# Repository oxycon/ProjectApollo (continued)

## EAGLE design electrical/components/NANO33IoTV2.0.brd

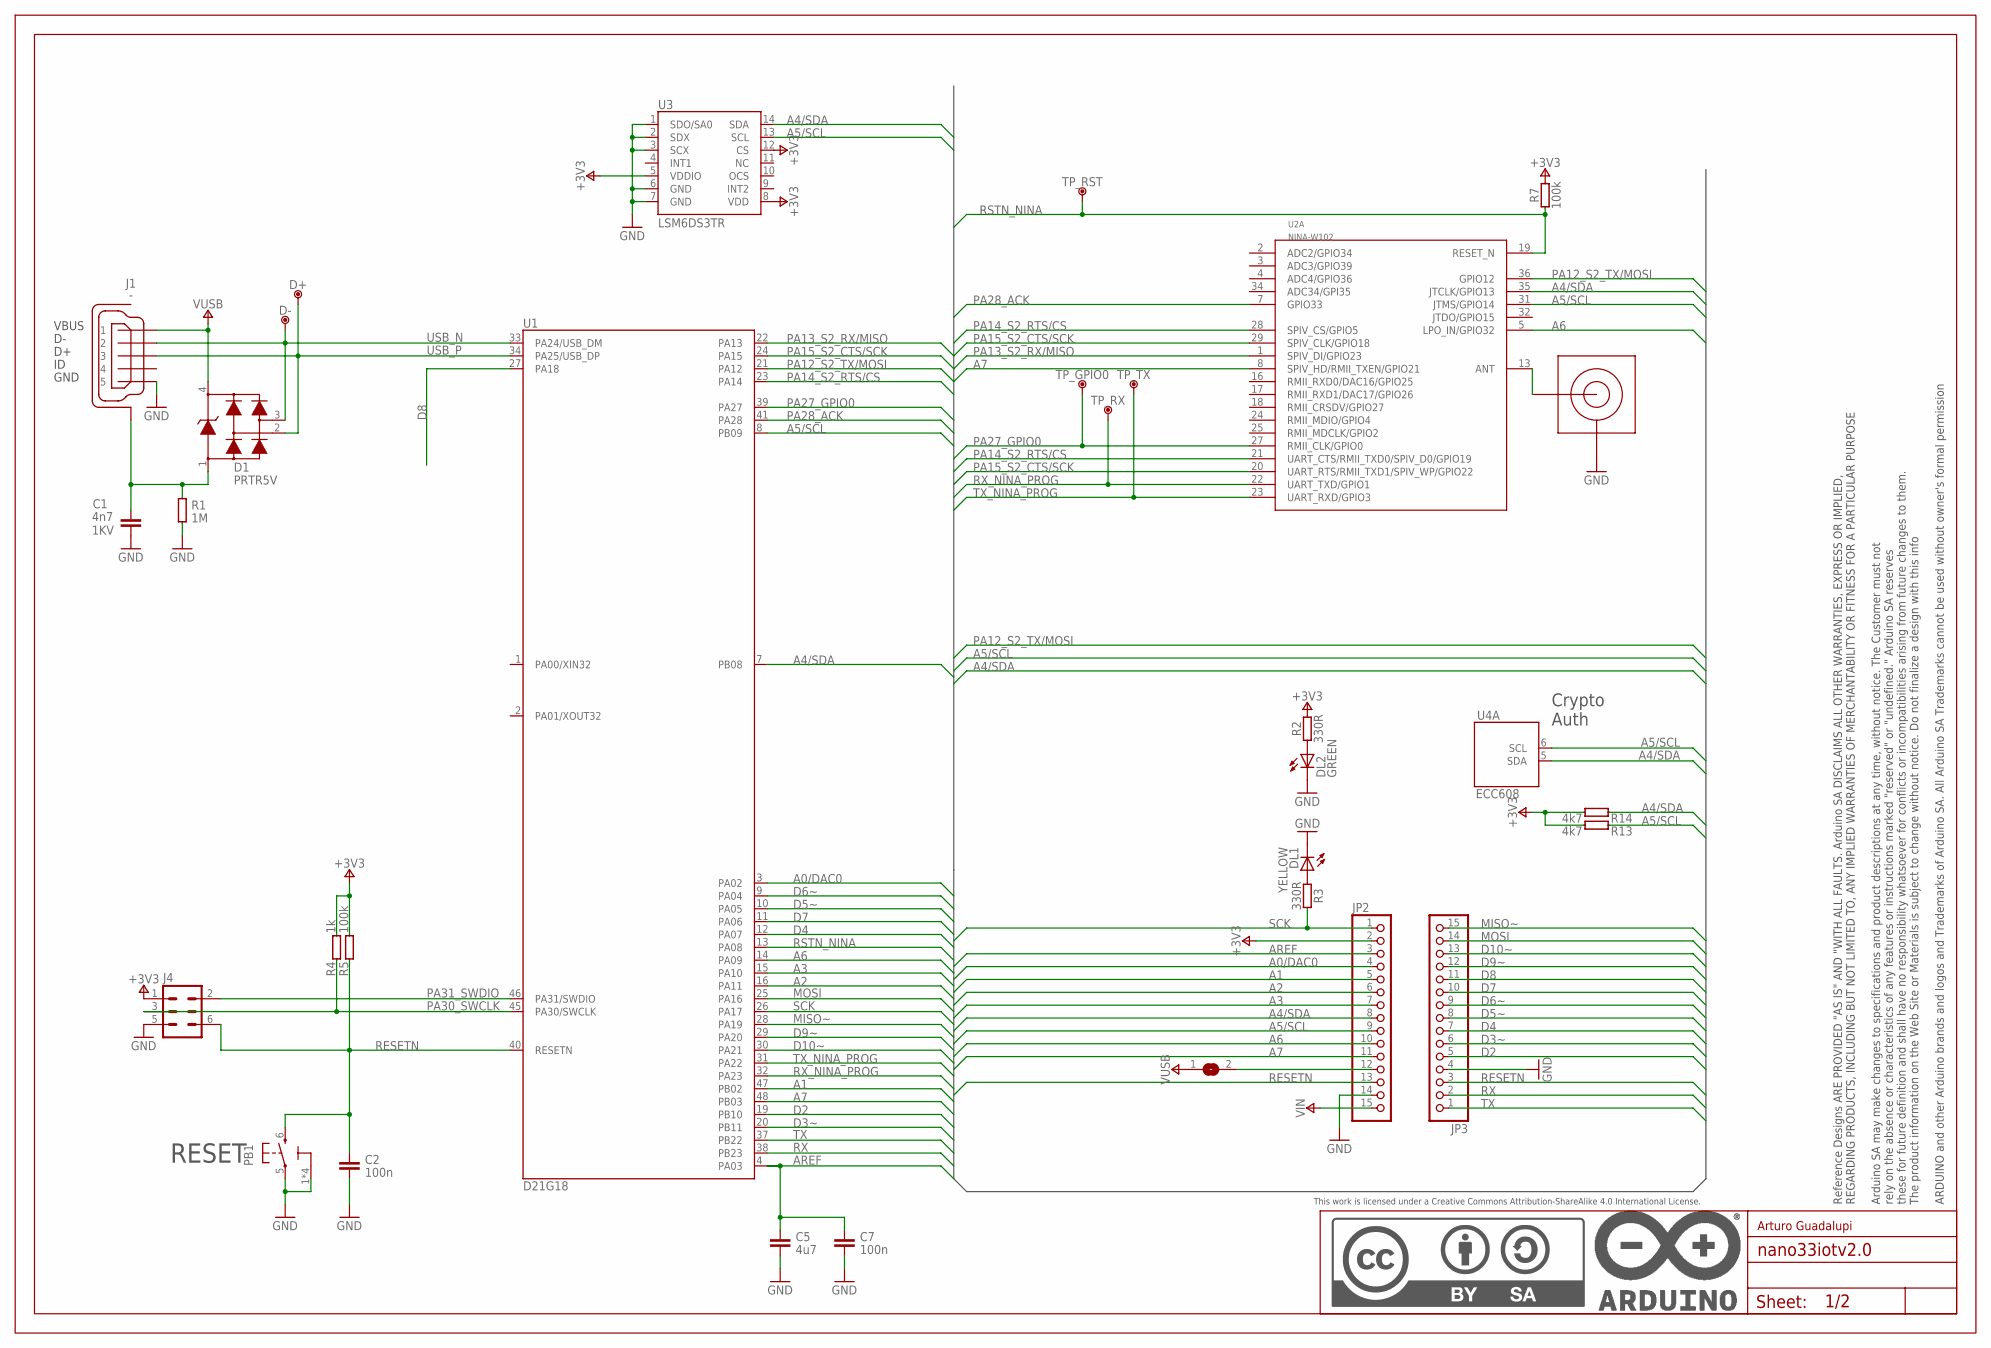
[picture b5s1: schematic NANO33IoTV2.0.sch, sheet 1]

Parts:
C1: 4n7; 0805-R2013X50N; VOLTAGE 1KV
C2, C7: 100n; 0402-1005X55N
C5: 4u7; 0402-1005X55N
D1: PRTR5V; SOT190P230X110-4N
D+: DNP; TP-1.00MM
D-: DNP; TP-1.00MM
DL1: YELLOW; LEDC1608X80N-AK
DL2: GREEN; LEDC1608X80N-AK
FRAME1: DNP; FRAME
J1: -; ZX62-AB-5PA
J3: DNP; U.FL-R-SMT-1(60)/NO_CREAM
J4: DNP; 2X03-TP1
JP2, JP3: PINHD-1X15-CASTELLATED; 1X15-CASTELL
PB1: PTS820; C&K_PTS820_NO_HOLES
R1: 1M; 0402-1005X55N
R2, R3: 330R; 0402-1005X55N
R4: 1k; 0402-1005X55N
R5, R7: 100k; 0402-1005X55N
R13, R14: 4k7; 0402-1005X55N
SJ1: DNP; SJ
TP_GPIO0: DNP; TP-0.8MM
TP_RST: DNP; TP-0.8MM
TP_RX: DNP; TP-0.8MM
TP_TX: DNP; TP-0.8MM
U1: D21G18; QFN50P700X700X90-49XN-EPSQ515
U2: NINA-W102; NINA-W1X
U3: LSM6DS3TR; LGA14L
U4: ECC608; SON50P300X200X60-9N-EP160X140

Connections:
+3V3: J4.1, JP2.2, R2.2, R4.2, R5.2, R7.2, R13.2, R14.2, U3.5 (VDDIO), U3.8 (VDD), U3.12 (CS); also elsewhere on the board
A0/DAC0: JP2.4, U1.3 (PA02)
A1: JP2.5, U1.47 (PB02)
A2: JP2.6, U1.16 (PA11)
A3: JP2.7, U1.15 (PA10)
A4/SDA: JP2.8, R14.1, U1.7 (PB08), U2.35 (JTCLK/GPIO13), U3.14 (SDA), U4.5 (SDA)
A5/SCL: JP2.9, R13.1, U1.8 (PB09), U2.31 (JTMS/GPIO14), U3.13 (SCL), U4.6 (SCL)
A6: JP2.10, U1.14 (PA09), U2.5 (LPO_IN/GPIO32)
A7: JP2.11, U1.48 (PB03), U2.8 (SPIV_HD/RMII_TXEN/GPIO21)
AREF: C5.1, C7.1, JP2.3, U1.4 (PA03)
D2: JP3.5, U1.19 (PB10)
D3~: JP3.6, U1.20 (PB11)
D4: JP3.7, U1.12 (PA07)
D5~: JP3.8, U1.10 (PA05)
D6~: JP3.9, U1.9 (PA04)
D7: JP3.10, U1.11 (PA06)
D8: JP3.11, U1.27 (PA18)
D9~: JP3.12, U1.29 (PA20)
D10~: JP3.13, U1.30 (PA21)
GND: C1.2, C2.2, C5.2, C7.2, DL1.C, DL2.C, J1.5, J3.GND1 (GND), J3.GND2 (GND), J4.5, JP2.14, JP3.4, PB1.1 (3), PB1.2 (3), PB1.3, PB1.4 (3), PB1.5 (1), R1.1, U3.1 (SDO/SA0), U3.2 (SDX), U3.3 (SCX), U3.6 (GND), U3.7 (GND); also elsewhere on the board
MISO~: JP3.15, U1.28 (PA19)
MOSI: JP3.14, U1.25 (PA16)
unnamed: C1.1, D1.1, J1.6 (SH), J1.7 (SH), J1.8 (SH), J1.9 (SH), J1.10 (SH), J1.11 (SH), R1.2
unnamed: DL2.A, R2.1
unnamed: DL1.A, R3.1
unnamed: J3.SIG, U2.13 (ANT)
unnamed: JP2.12, SJ1.2
PA12_S2_TX/MOSI: U1.21 (PA12), U2.36 (GPIO12)
PA13_S2_RX/MISO: U1.22 (PA13), U2.1 (SPIV_DI/GPIO23)
PA14_S2_RTS/CS: U1.23 (PA14), U2.21 (UART_CTS/RMII_TXD0/SPIV_D0/GPIO19), U2.28 (SPIV_CS/GPIO5)
PA15_S2_CTS/SCK: U1.24 (PA15), U2.20 (UART_RTS/RMII_TXD1/SPIV_WP/GPIO22), U2.29 (SPIV_CLK/GPIO18)
PA27_GPIO0: TP_GPIO0.X, U1.39 (PA27), U2.27 (RMII_CLK/GPIO0)
PA28_ACK: U1.41 (PA28), U2.7 (GPIO33)
PA30_SWCLK: J4.3, R4.1, U1.45 (PA30/SWCLK)
PA31_SWDIO: J4.2, U1.46 (PA31/SWDIO)
RESETN: C2.1, J4.6, JP2.13, JP3.3, PB1.6 (2), R5.1, U1.40 (RESETN)
RSTN_NINA: R7.1, TP_RST.X, U1.13 (PA08), U2.19 (RESET_N)
RX: JP3.2, U1.38 (PB23)
RX_NINA_PROG: TP_RX.X, U1.32 (PA23), U2.22 (UART_TXD/GPIO1)
SCK: JP2.1, R3.2, U1.26 (PA17)
TX: JP3.1, U1.37 (PB22)
TX_NINA_PROG: TP_TX.X, U1.31 (PA22), U2.23 (UART_RXD/GPIO3)
USB_N: D1.3, D-.X, J1.2, U1.33 (PA24/USB_DM)
USB_P: D1.2, D+.X, J1.3, U1.34 (PA25/USB_DP)
VIN: JP2.15; also elsewhere on the board
VUSB: D1.4, J1.1, SJ1.1; also elsewhere on the board

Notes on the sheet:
RESET
Crypto Auth
Arturo Guadalupi

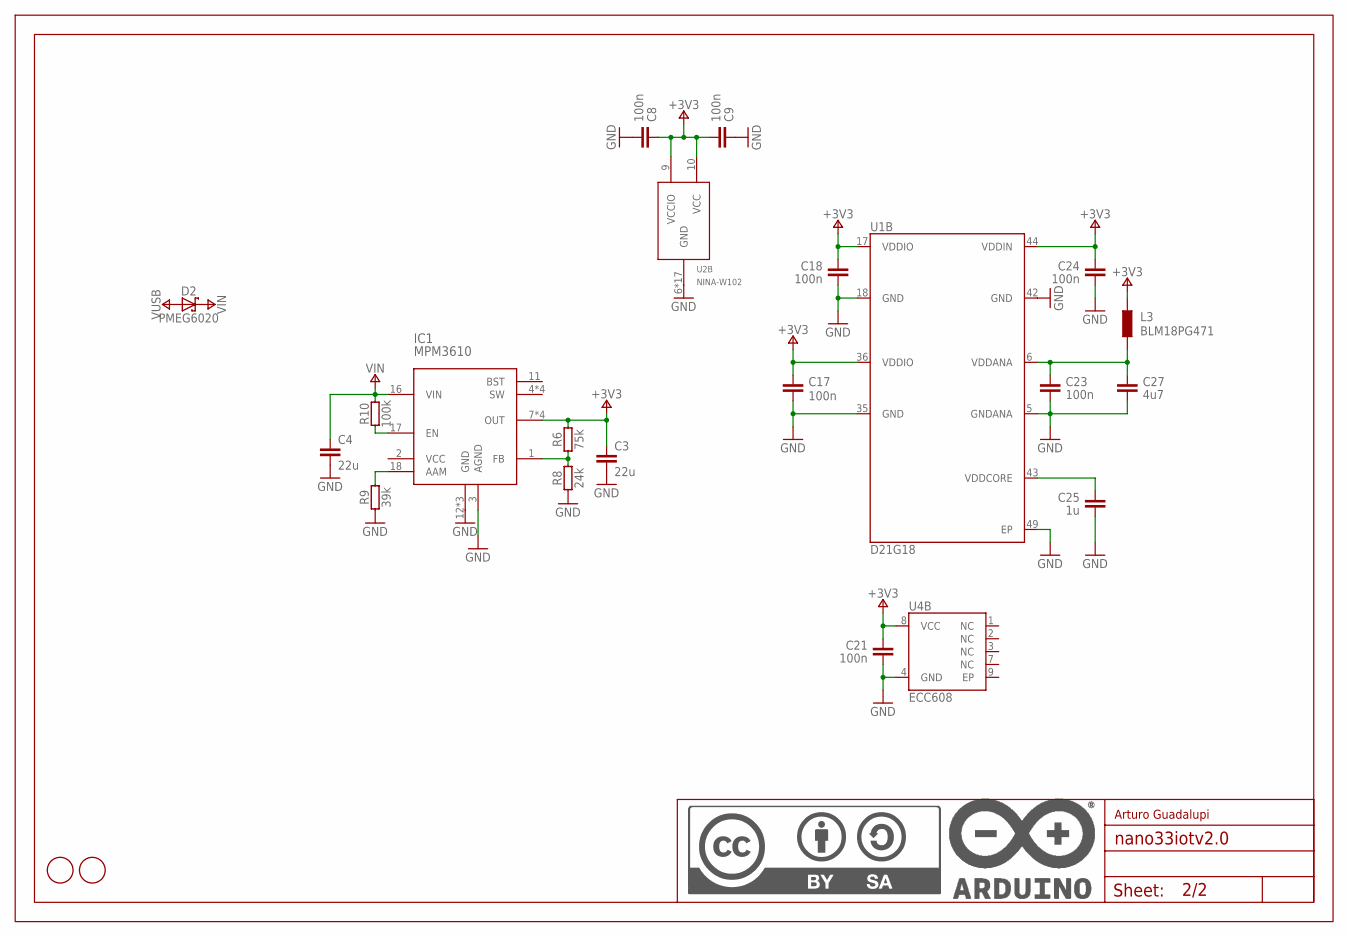
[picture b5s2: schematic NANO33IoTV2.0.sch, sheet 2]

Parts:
C3, C4: 22u; 0805-R2013X50N
C8, C9, C17, C18, C21, C23, C24: 100n; 0402-1005X55N
C25: 1u; 0402-1005X55N
C27: 4u7; 0603-1608X90N
D2: PMEG6020; SODFL3517X110N
FD1, FD2: DNP; FD-1-1.5
IC1: MPM3610
L3: BLM18PG471; 0603-1608X90N
R6: 75k; 0402-1005X55N
R8: 24k; 0402-1005X55N
R9: 39k; 0402-1005X55N
R10: 100k; 0402-1005X55N
U1: D21G18; QFN50P700X700X90-49XN-EPSQ515
U2: NINA-W102; NINA-W1X
U4: ECC608; SON50P300X200X60-9N-EP160X140
U$1: DNP; FRAME

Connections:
+3V3: C3.1, C8.1, C9.2, C17.1, C18.1, C21.1, C24.1, IC1.7 (OUT), IC1.8 (OUT), IC1.9 (OUT), IC1.20 (OUT), L3.1, R6.2, U1.17 (VDDIO), U1.36 (VDDIO), U1.44 (VDDIN), U2.9 (VCCIO), U2.10 (VCC), U4.8 (VCC); also elsewhere on the board
GND: C3.2, C4.2, C8.2, C9.1, C17.2, C18.2, C21.2, C23.2, C24.2, C25.2, C27.2, IC1.3 (AGND), IC1.12 (GND), IC1.13 (GND), IC1.14 (GND), R8.1, R9.1, U1.5 (GNDANA), U1.18 (GND), U1.35 (GND), U1.42 (GND), U1.49 (EP), U2.6 (GND), U2.12 (GND), U2.14 (GND), U2.26 (GND), U2.30 (GND), U2.GND@1 (GND), U2.GND@2 (GND), U2.GND@3 (GND), U2.GND@4 (GND), U2.GND@5 (GND), U2.GND@6 (GND), U2.GND@7 (GND), U2.GND@8 (GND), U2.GND@9 (GND), U2.GND@10 (GND), U2.GND@11 (GND), U2.GND@12 (GND), U4.4 (GND); also elsewhere on the board
N17852357: C23.1, C27.1, L3.2, U1.6 (VDDANA)
N17852431: C25.1, U1.43 (VDDCORE)
unnamed: IC1.1 (FB), R6.1, R8.2
unnamed: IC1.18 (AAM), R9.2
unnamed: IC1.17 (EN), R10.1
VIN: C4.1, D2.C, IC1.16 (VIN), R10.2; also elsewhere on the board
VUSB: D2.A; also elsewhere on the board

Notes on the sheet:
Arturo Guadalupi

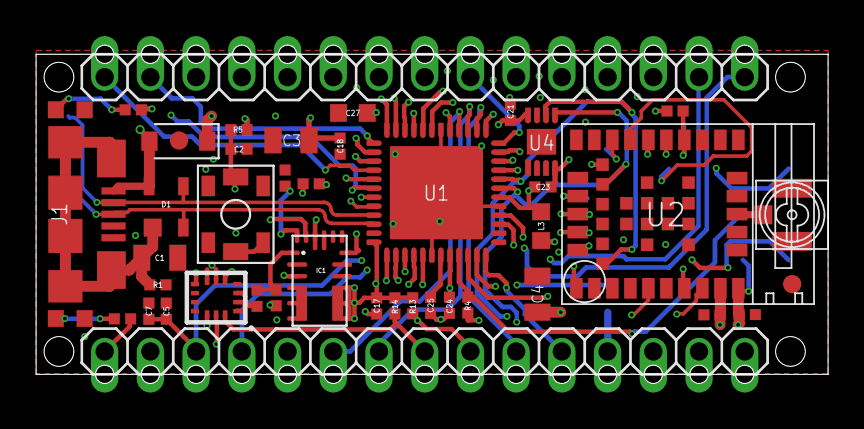
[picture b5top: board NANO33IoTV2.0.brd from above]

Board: 4 copper layers, 44.0 x 17.8 mm, 54 parts (1 on the bottom side), 51 nets.

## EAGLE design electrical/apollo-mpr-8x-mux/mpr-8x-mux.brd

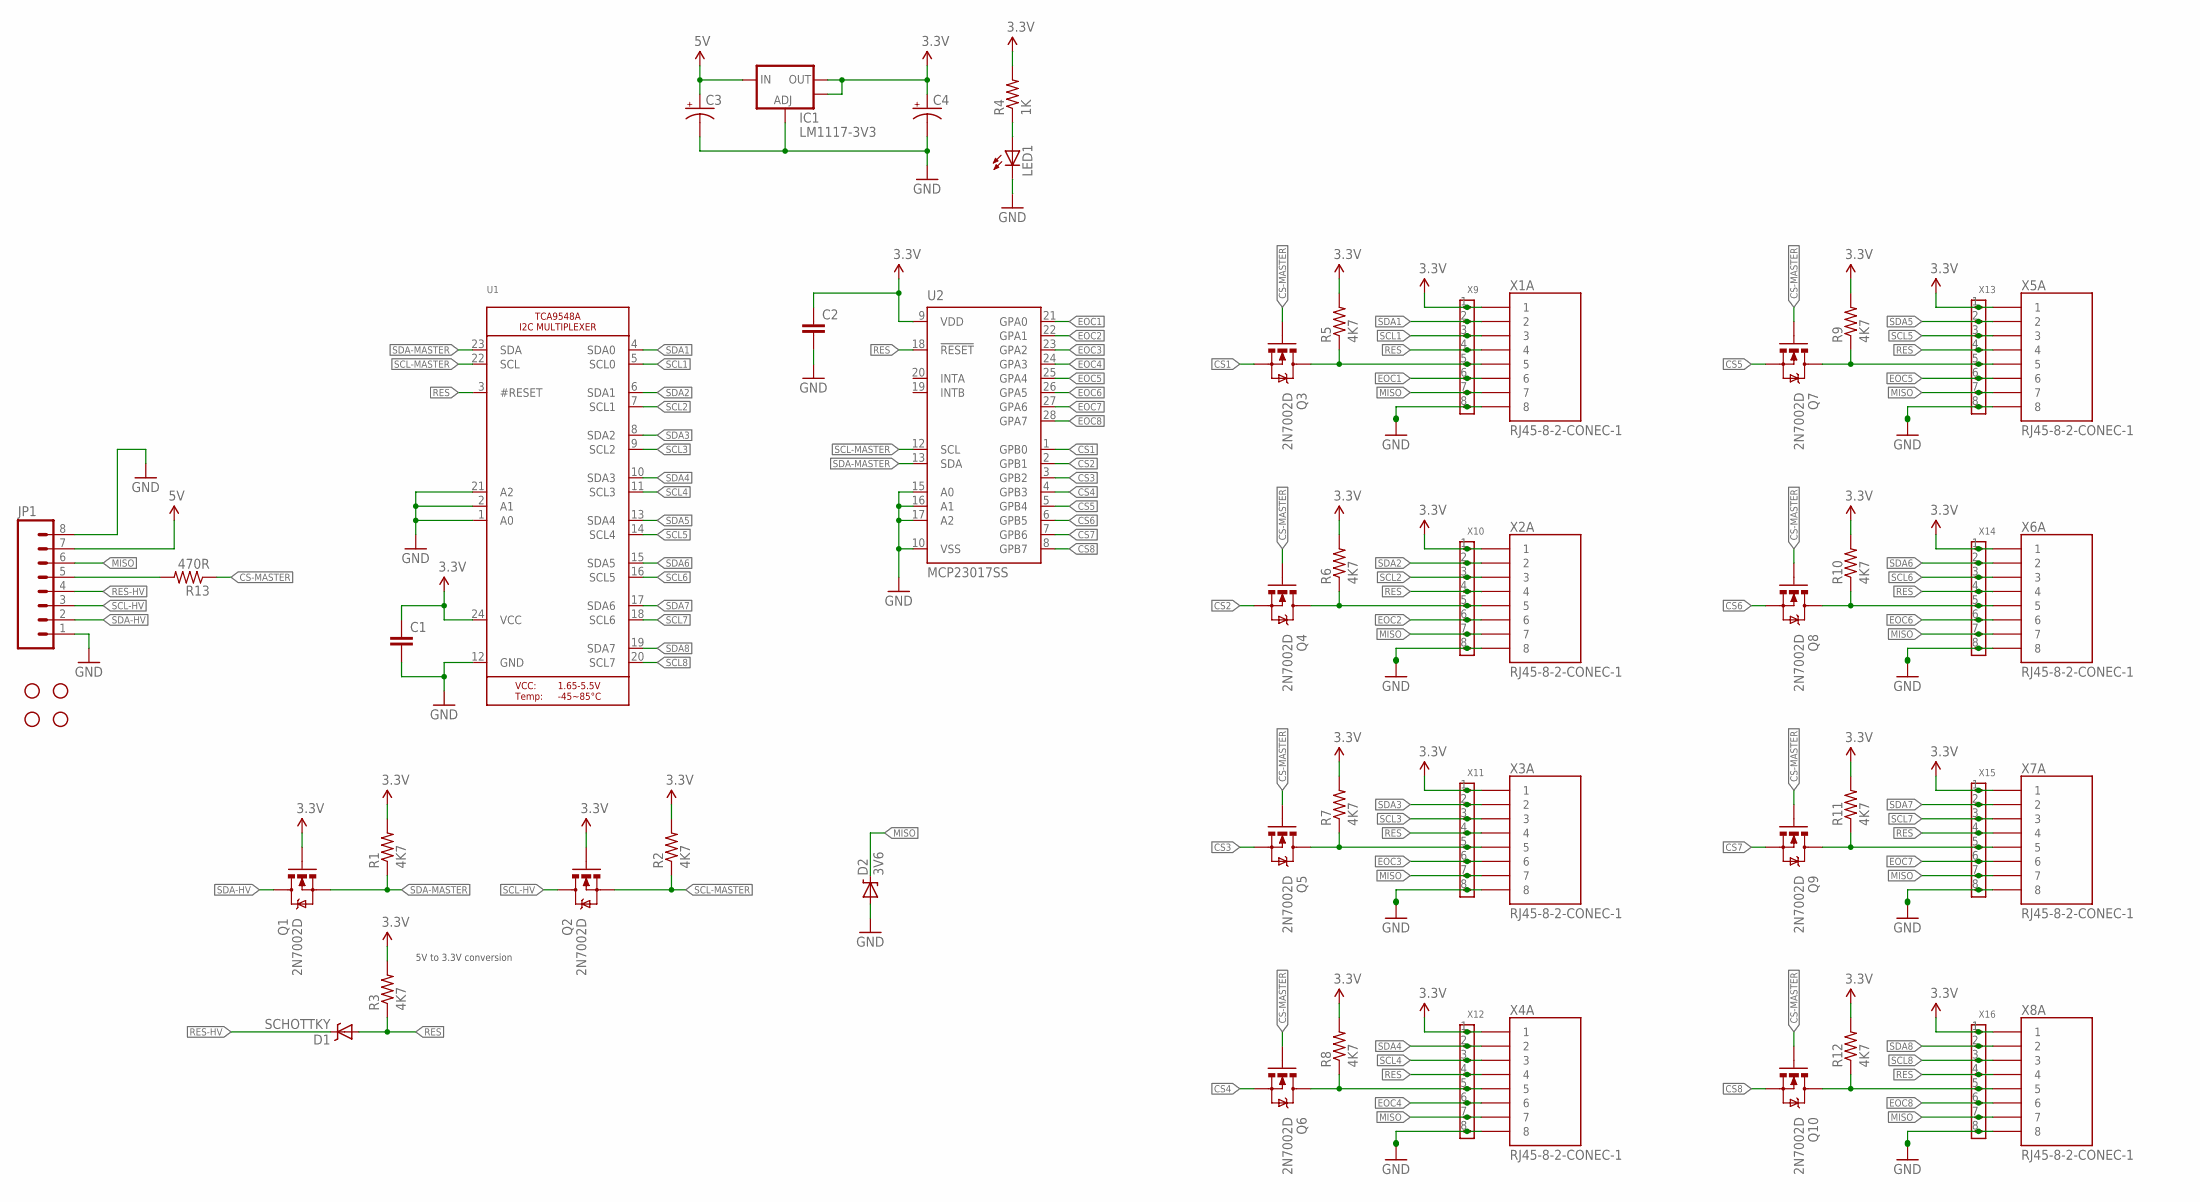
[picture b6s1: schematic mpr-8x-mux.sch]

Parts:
C1, C2: CAP0805; 0805
C3, C4: CAP_POL1206-KIT; EIA3216-KIT
D1: SCHOTTKY; SOD-323
D2: 3V6; SOD-323
IC1: LM1117-3V3; SOT223
JP1: M081X08; 1X08
JP2, JP3, JP4, JP5: STAND-OFF
LED1: LED0603; LED-0603
Q1, Q2, Q3, Q4, Q5, Q6, Q7, Q8, Q9, Q10: 2N7002D; SOT23-3
R1, R2, R3, R5, R6, R7, R8, R9, R10, R11, R12: 4K7; 0805
R4: 1K; 0805
R13: 470R; 0805
U1: TCA9548A; TSSOP24
U2: MCP23017SS; SSOP28
X1, X2, X3, X4, X5, X6, X7, X8: RJ45-8-2-CONEC-1; CONEC-33TS3004ST-88001
X9, X10, X11, X12, X13, X14, X15, X16: TP-GROUP-X8-2X04; 2X4

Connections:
3.3V: C1.1, C2.1, C4.A (+), IC1.2 (OUT), IC1.4 (OUT), Q1.1 (G), Q2.1 (G), R1.2, R2.2, R3.2, R4.2, R5.2, R6.2, R7.2, R8.2, R9.2, R10.2, R11.2, R12.2, U1.24 (VCC), U2.9 (VDD), X1.1, X2.1, X3.1, X4.1, X5.1, X6.1, X7.1, X8.1, X9.1, X10.1, X11.1, X12.1, X13.1, X14.1, X15.1, X16.1
5V: C3.A (+), IC1.3 (IN), JP1.7
CS1: Q3.2 (S), U2.1 (GPB0)
CS2: Q4.2 (S), U2.2 (GPB1)
CS3: Q5.2 (S), U2.3 (GPB2)
CS4: Q6.2 (S), U2.4 (GPB3)
CS5: Q7.2 (S), U2.5 (GPB4)
CS6: Q8.2 (S), U2.6 (GPB5)
CS7: Q9.2 (S), U2.7 (GPB6)
CS8: Q10.2 (S), U2.8 (GPB7)
CS-MASTER: Q3.1 (G), Q4.1 (G), Q5.1 (G), Q6.1 (G), Q7.1 (G), Q8.1 (G), Q9.1 (G), Q10.1 (G), R13.1
EOC1: U2.21 (GPA0), X1.6, X9.6
EOC2: U2.22 (GPA1), X2.6, X10.6
EOC3: U2.23 (GPA2), X3.6, X11.6
EOC4: U2.24 (GPA3), X4.6, X12.6
EOC5: U2.25 (GPA4), X5.6, X13.6
EOC6: U2.26 (GPA5), X6.6, X14.6
EOC7: U2.27 (GPA6), X7.6, X15.6
EOC8: U2.28 (GPA7), X8.6, X16.6
GND: C1.2, C2.2, C3.C (-), C4.C (-), D2.2 (A), IC1.1 (ADJ), JP1.1, JP1.8, LED1.C, U1.1 (A0), U1.2 (A1), U1.12 (GND), U1.21 (A2), U2.10 (VSS), U2.15 (A0), U2.16 (A1), U2.17 (A2), X1.8, X1.M1, X1.M2, X2.8, X2.M1, X2.M2, X3.8, X3.M1, X3.M2, X4.8, X4.M1, X4.M2, X5.8, X5.M1, X5.M2, X6.8, X6.M1, X6.M2, X7.8, X7.M1, X7.M2, X8.8, X8.M1, X8.M2, X9.8, X10.8, X11.8, X12.8, X13.8, X14.8, X15.8, X16.8
MISO: D2.1 (C), JP1.6, X1.7, X2.7, X3.7, X4.7, X5.7, X6.7, X7.7, X8.7, X9.7, X10.7, X11.7, X12.7, X13.7, X14.7, X15.7, X16.7
unnamed: LED1.A, R4.1
unnamed: Q7.3 (D), R9.1, X5.5, X13.5
unnamed: Q8.3 (D), R10.1, X6.5, X14.5
unnamed: Q9.3 (D), R11.1, X7.5, X15.5
unnamed: Q10.3 (D), R12.1, X8.5, X16.5
unnamed: Q6.3 (D), R8.1, X4.5, X12.5
unnamed: Q5.3 (D), R7.1, X3.5, X11.5
unnamed: Q4.3 (D), R6.1, X2.5, X10.5
unnamed: Q3.3 (D), R5.1, X1.5, X9.5
unnamed: JP1.5, R13.2
RES: D1.2 (A), R3.1, U1.3 (#RESET), U2.18 (!RESET), X1.4, X2.4, X3.4, X4.4, X5.4, X6.4, X7.4, X8.4, X9.4, X10.4, X11.4, X12.4, X13.4, X14.4, X15.4, X16.4
RES-HV: D1.1 (C), JP1.4
SCL1: U1.5 (SCL0), X1.3, X9.3
SCL2: U1.7 (SCL1), X2.3, X10.3
SCL3: U1.9 (SCL2), X3.3, X11.3
SCL4: U1.11 (SCL3), X4.3, X12.3
SCL5: U1.14 (SCL4), X5.3, X13.3
SCL6: U1.16 (SCL5), X6.3, X14.3
SCL7: U1.18 (SCL6), X7.3, X15.3
SCL8: U1.20 (SCL7), X8.3, X16.3
SCL-HV: JP1.3, Q2.3 (D)
SCL-MASTER: Q2.2 (S), R2.1, U1.22 (SCL), U2.12 (SCL)
SDA1: U1.4 (SDA0), X1.2, X9.2
SDA2: U1.6 (SDA1), X2.2, X10.2
SDA3: U1.8 (SDA2), X3.2, X11.2
SDA4: U1.10 (SDA3), X4.2, X12.2
SDA5: U1.13 (SDA4), X5.2, X13.2
SDA6: U1.15 (SDA5), X6.2, X14.2
SDA7: U1.17 (SDA6), X7.2, X15.2
SDA8: U1.19 (SDA7), X8.2, X16.2
SDA-HV: JP1.2, Q1.3 (D)
SDA-MASTER: Q1.2 (S), R1.1, U1.23 (SDA), U2.13 (SDA)

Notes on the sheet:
5V to 3.3V conversion

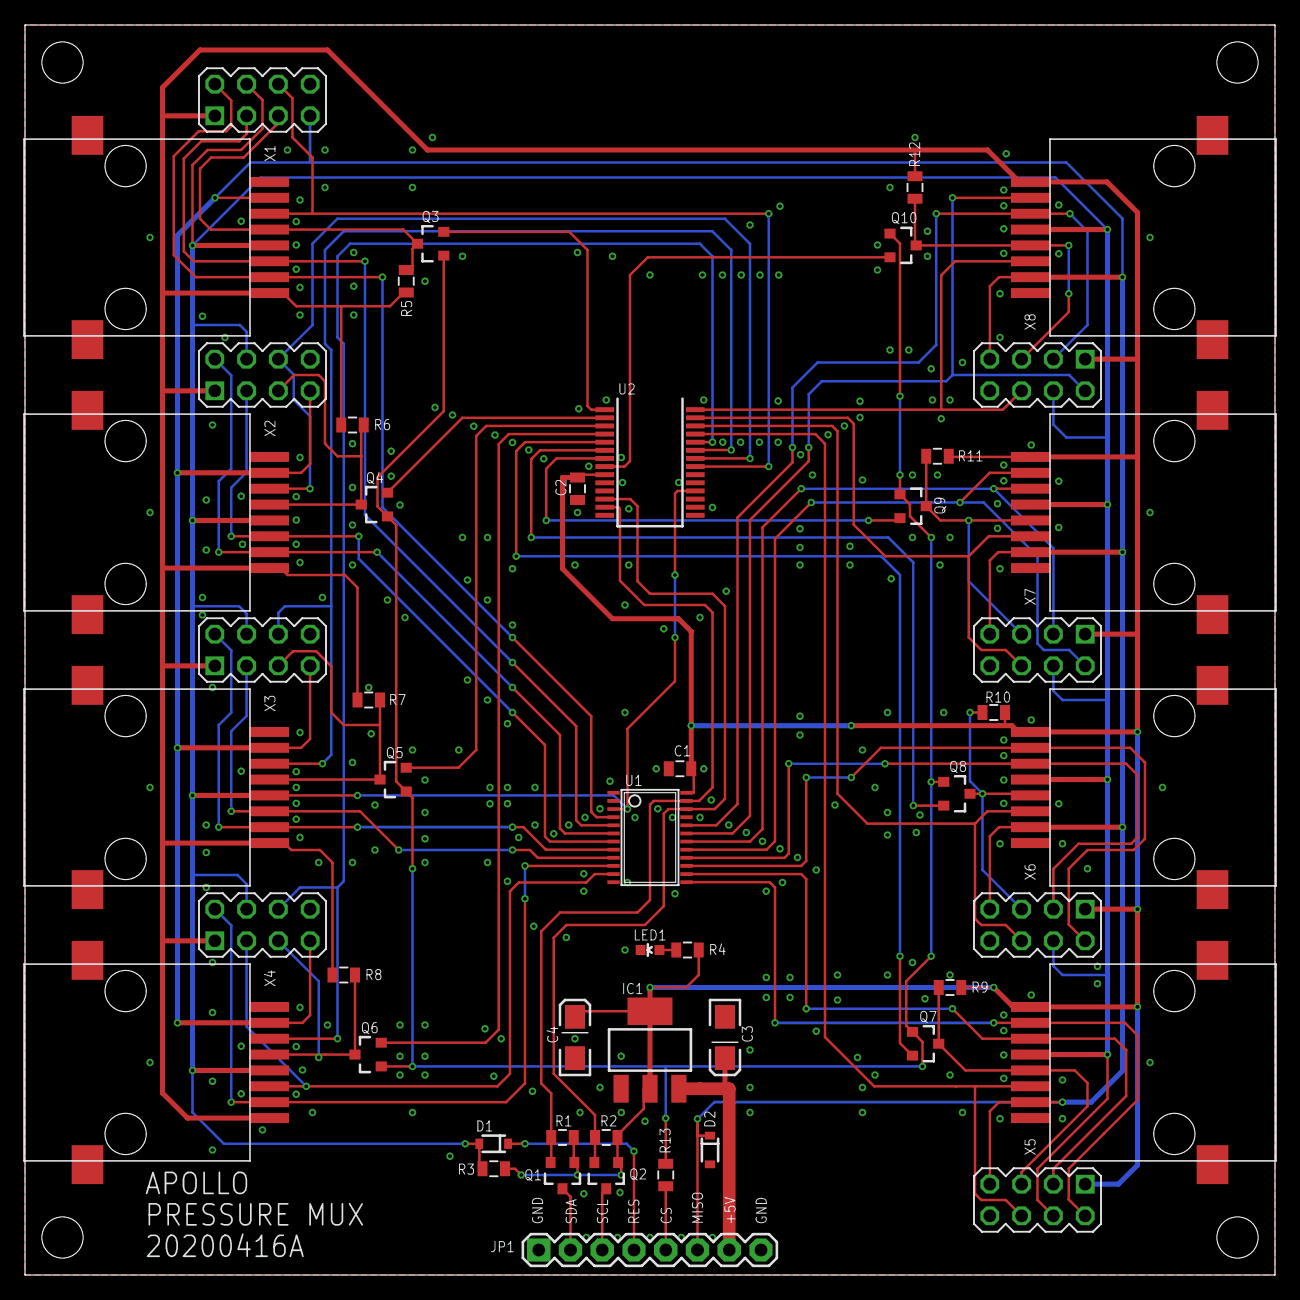
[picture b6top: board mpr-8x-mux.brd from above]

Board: 2 copper layers, 100.0 x 100.0 mm, 54 parts (0 on the bottom side), 53 nets.

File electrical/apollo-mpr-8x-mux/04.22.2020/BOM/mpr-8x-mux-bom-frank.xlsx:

Qty | Designator | Footprint | Comment | LCSC Part # | Description (optional)
2 | C1, C2 | C0805 | 100n | C49678 | Capacitor
2 | C3, C4 | C1206 | 10u | C127946 | Capacitor Polarized
1 | LED1 | CHIP_LED0603 | LED | C205443 | LED
1 | U1 | TSSOP-24 | TCA9548A | C130026 | TCA9548A I2C Multiplexer
1 | R4 | R0805 | 1K | C17513 | Resistor
10 | Q1, Q2, Q3, Q4, Q5, Q6, Q7, Q8, Q9, Q10 | SOT-23-3 | 2N7002 | C12779
1 | D2 | SOD-323 | 3V6 | C12453 | Zener Diode
1 | R13 | R0805 | 470R | C17710 | Resistor
11 | R1, R2, R3, R5, R6, R7, R8, R9, R10, R11, R12 | R0805 | 4K7 | C17673 | Resistor
1 | IC1 | SOT-223 | LM1117-3V3 | C347222 | Voltage Regulator LM1117
1 | D1 | SOD-323 | SCHOTTKY | C64886 | Schottky Diode

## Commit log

2020-03-18 add license
2020-03-20 Combined commit
2020-03-22 add Arduino source code for valve cycling
2020-03-22 move file in prototype subdirectory
2020-03-22 comments/fixes
2020-03-22 comments/fixes 2
2020-03-22 fix materials
2020-03-22 add schematic
2020-03-22 add PDF exports
2020-03-22 add more drawings, PDF
2020-03-22 move .scad file to Drawings
2020-03-22 Create disclaimer
2020-03-22 Update disclaimer
2020-03-22 add more text to drawings
2020-03-22 update video playlist
2020-03-22 add Invacare Platinum XL manuals
2020-03-22 move manuals in separate directory
2020-03-23 rename PDF manuals
2020-03-24 initial set of files with very little progress
2020-04-06 initial files
2020-04-07 add FAN support for Prototype v2
2020-04-07 add Gerber/SMTA order info for JLCPCB
2020-04-07 add picture
2020-04-08 initial drawings
2020-04-08 fixes/reorganization
2020-04-09 photos folder reorg
2020-04-09 reorg materials/BOM/drawings pdf
2020-04-09 move docs
2020-04-10 add Gasboard datasheets
2020-04-11 code for Arduino use of gasboard7500E, tested and working
2020-04-12 DIY version of PCB sort of done, require review
2020-04-12 bigger PCB preview image
2020-04-12 added more spare pins to i2c header
2020-04-12 fixed wrong battery type
2020-04-12 library added adafruit mprls
2020-04-12 changed to use Adafruit MPRLS
2020-04-12 added EOC signal to A0
2020-04-12 all components now top side
2020-04-13 added a fan header
2020-04-14 started to write some code
2020-04-14 added SPI signals to MPR breakout
2020-04-15 MPR 8x mux schematic and PCB
2020-04-15 add build instructions prototype v2
2020-04-16 work in progress code
2020-04-16 fixed chip select problem with mosfets
2020-04-16 minor doc fixes
2020-04-16 added 2x4 header to mpr-8x-mux pcb
2020-04-16 minor tweaks for ctrl pcb before fab
2020-04-16 ctrl pcb, more silk text, added extra ADC pins
2020-04-17 work in progress code (syntax fixes and tested some stuff)
2020-04-18 work in progress code (tested many functions)
2020-04-25 fix doc
2020-04-28 add O2 sensor Arduino code, check-in gerbers
2020-04-28 add better diagnostics
2020-04-28 add valve timing code and potentiometer hookup
2020-04-28 fix frequent timing change bug
2020-05-06 add PDF version of building v2 prototype
2020-05-06 add PDF version of building v2 prototype (2)
2020-05-08 add more info to README.md, other fixes
2020-05-15 add relief valve button
2020-05-17 add motorized valve Arduino code
2020-05-26 added TE MS5837 breakout PCB
2020-05-27 add gerbers to separate directory
2020-05-27 resize TE board, add mounting holes
2020-05-27 resize MPR board, add mounting holes
2020-05-27 move old Gerbers into dedicated directory
2020-05-27 add docs
2020-05-27 minor fixes (dimensions)
2020-05-27 add MPR sensor test code
2020-05-27 add ops risk analysis
2020-05-27 add BOM for apollo-ctrl
2020-05-31 making pressure sensor a lot more reliable
2020-06-02 add needle valve actuator and the MPR pressure together
2020-06-02 add PID control part 1
2020-06-02 PID controller works!
2020-06-06 add OLED display
2020-06-10 add rotary encoder to tweak target pressure
2020-06-14 minor fixes
2020-06-16 adding simulation code
2020-06-16 changed to md format
2020-06-16 better formatting of README
2020-07-10 add some docs
2020-07-11 Apollo v4 control board.docx
2020-07-16 add PPTs
2020-07-17 new changes
2020-07-17 new changes 2
2020-07-19 file reorg per prototype
2020-07-20 move Apollo v4 docs
2020-07-20 prototype v3 reorg
2020-07-20 initial doc for v4
2020-07-20 doc upgrades
2020-07-20 add PDFs
2020-07-28 add various docs
2020-07-28 add block diagram v4.01
2020-07-28 new PCB library with ESP32, LCD, and DRV8806
2020-07-29 [Early prototype for refactoring the simulation into a OpenAI gym-compatible API to represent the Apollo MDP][Non-sequential version][Need much more testing]
2020-07-29 Fixed import issues from parent directory
2020-07-29 Removing orifice controls from the actions space; action_space dim is now 2 corresponding to cycle_time and vent_time
2020-07-29 added bonsai stuff
2020-07-30 Start of V4 firmware
2020-07-30 Added Secrets.h, which is normally ignored
2020-07-30 Changing reward from prod_y to container_y
2020-07-30 Added serial port demo script
2020-07-30 template boards
2020-07-30 new version of template board
2020-07-30 fix template board symbols
2020-07-30 fix template board dimensions
2020-07-30 add HuskySat-1 credits
2020-07-30 simulator v1
2020-07-30 Start of display support
2020-07-30 re-added Secrets.h
2020-07-30 works with simulator
2020-07-30 merging to master of original
2020-07-30 Created a configurable non blocking state machine for the valve cycle.
2020-07-31 Control valves and concentrator from CLI
2020-07-31 Save state and more CLI commands
2020-07-31 - More CLI commands to configure WIFI and load preferences - CLI hex and binary parser - Moved valve pins - Removed EEPROM delays - Configure button pin
2020-07-31 Added Pinout document and libraries
2020-08-01 Added Oxygen Sensor logic
2020-08-01 Updated readme.txt with CLI commands
2020-08-01 Allow debug logging to be disabled
2020-08-02 Renamed TcpClient into TcpConnection and turned it into a Stream
2020-08-02 Allow debug stream to be taken over by TCP connection.
2020-08-02 Added document that suggest to use 2 types of zeolite
2020-08-02 Better debug status
2020-08-02 added support for valve drivers DRV-8806
2020-08-03 move connector bus to the edge of the board
2020-08-05 Initial version of the Apollo V4 modular valve board. No layout, and no header connections, pending pinout decisions with the controller board.
2020-08-05 Added commands to get configuration and sensor data as JSON.
2020-08-06 Added display brightness control
2020-08-06 Show sensor data on display
2020-08-07 Update display with sensor data
2020-08-07 Added BME280 humidity/pressure sensor
2020-08-07 Added Sensor base class
2020-08-08 Added SHTC3 humidity sensor
2020-08-08 Added HDC2080 humidity sensor
2020-08-08 Created sensor manager
2020-08-09 Added CLI humidity sensor support
2020-08-12 Fixed Valve SPI channel conflicting with LCD
2020-08-12 Cleaned up some unnecessary oxygen sensor logic + some small display bug fixes
2020-08-12 Added bar graphs for oxygen and flow
2020-08-12 Update valve board and proposed a pinout for Apollo v4
2020-08-14 Work on larger display ILI9488
2020-08-15 Added TCS34725 color sensor
2020-08-15 Drive valves from timer interrupt instrad of main loop to avoid jitter
2020-08-16 Changed DRV default count to 1 and SPI frequency to 10MHz
2020-08-16 Support non automatic Gasboard-7500E oxygen sensors
2020-08-18 PCB experiments
2020-08-19 more details for the Apollo v4
2020-08-19 rename Apollo v4 control board.docx -> Apollo v4 control box.docx
2020-08-19 add pdf version for Apollo v4 control box.pdf
2020-08-20 Added MPRLS pressure sensor and work on sensor management
2020-08-23 added HTU21D humidity sensor
2020-08-24 Start of error infrastructure + color sensor address config
2020-08-25 start of touch controller support + made date/time format configurable
2020-08-25 Results of crash investigation
2020-08-28 Initial version of the controller board, ESP32-PICO-KIT edition. Proposed GPIO mapping also updated in the document to break out all otherwise unused pins of the ESP32.
2020-08-28 work on error log, sensor errors, error infra
2020-08-29 fixes
2020-08-30 work on touch buttons + valve control buttons
2020-09-05 add 3.5 display sample files
2020-09-08 - Added CYCLE-DURATIONS command to get/set all durations at once - Additional pressure sensor error check - Increased oxygen sensor sample rate
2020-09-08 Renamed cycle to stage
2020-09-09 Added stats collection and stats logging
2020-09-09 Added concentrator data logging
2020-09-17 add Apollo v4 docs/presentation for COSMIC meeting
2020-09-17 add Apollo v4 docs/presentation for COSMIC meeting 2
2020-09-17 add Apollo v4 docs/presentation for COSMIC meeting 4
2020-09-17 add Apollo v4 docs/presentation for COSMIC meeting 5
2020-09-18 add Apollo v4 docs/presentation for COSMIC meeting 6
2020-09-24 add sample code
2020-10-31 add Oxikit presentation
2020-11-02 Work on self calibration
2020-11-02 Added disclaimer and license test
2020-11-02 Updated display library
2020-11-07 add PPT v08
2020-12-07 initial flow control code
2020-12-13 add more docs
2021-01-29 Update valve board schematic
2021-02-08 Remove stepper driver from Valve board to be moved to a future Stepper board
2021-03-09 add v09 ppt
2021-03-09 v09 ppt updates
2021-03-11 add Project Apollo - v09.pdf
2021-03-11 add license and gasboard code for the flow controller
2021-03-13 Add initial layout for the Valve board. Fully routed, with plenty of room to potentially add the steppers back
2021-03-14 add presentation @hack4good spring 2021
2021-03-19 Add stepper drivers to the valve board schematic. No guarantee that they fit, but if they do not another board can be made.
2021-03-20 moved simulation directory into its own repo - https://github.com/oxycon/ProjectApolloSimulation
2021-03-20 add README.md for simulation code pointing to its own repository
2021-03-23 Remove the Trinamics bipolar stepper drivers and add unipolar stepper drivers instead (as the motors are cheaper and more available).
2021-03-27 First layout pass for complete valve board
2021-03-29 Add PulseOximeterService to connect and read a BerryMed PulseOximeter
2021-03-29 Add file headers. Include PulseOximeterService into the v4 firmware
2021-04-01 Clean up valve board silkscreen and change diodes to SOD-123
2021-04-26 Enable Arduino Nano 33 support for PulseOximeterService
2021-04-28 Switch Apollo control board to use discrete SPI LCD and no M5-Stack
2021-04-28 Add buzzer to Apollo control board and move capacitor away from the USB port
2021-05-24 adding logos
2021-05-24 remove pdf copies
2021-05-28 add presentation for RespiCon 2021
2021-06-29 add JLCPCB DRU (inspired from OshPark)
2021-06-29 DRC error-free
2021-07-07 added Gerbers for control board v4 JLCPCB order
2021-07-07 added some docs
2021-07-07 added more docs
2021-08-26 make firmware compile for PICO
2021-08-27 add PICO port assignments
2021-09-26 Update TFT LCD pinout for version 2 of the Adafruit breakout board
2021-09-26 Add touch screen connectors on control PCB, and roll up fab to B
2021-11-18 disable wifi, sensors and the concentrator to prevent errors on barebone board
2021-11-18 add ESP32-PICO-KIT_V4.1 info
2021-12-24 making display work
2022-01-14 add DRV8803 sample code from TI
2022-02-12 remove lfs, add some jpg/pdf
2022-08-03 add mic2250
